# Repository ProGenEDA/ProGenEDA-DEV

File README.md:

# ProGenEDA

ProGenEDA is a development repository for deterministic, donor-aware EDA
generation. A backend receives one canonical circuit JSON document, resolves
only supported native records, produces an editable project, and retains
machine-readable validation evidence beside the result.

This repository contains independent backends for Proteus, KiCad, EasyEDA Pro,
and LTspice. They share the canonical circuit intent but do not depend on one
another at runtime.

## Backends

| Backend | Native output | Current entry point | Scope summary |
| --- | --- | --- | --- |
| Proteus | `.pdsprj` | [`proteus/active/`](proteus/active/) | Donor-backed placement, bounded terminal attachment, value editing, and local loader evidence. |
| KiCad | `.kicad_pro`, `.kicad_sch`, optional `.kicad_pcb` | [`kicad/`](kicad/) | Canonical JSON repair, source-backed schematic generation, combination routing, validation, and bounded two-layer PCB output. |
| EasyEDA Pro | `.eprj` | [`Easyeda/`](Easyeda/) | Native SQLite project generation using audited source records, compact schematic routing, and bounded PCB generation. |
| Altium | `.PrjPcb` + source-backed `.SchDoc`, packaged as ZIP | [`Altium/`](Altium/) | Full direct native schematic pipeline: repair, values, source selection, placement, arrangement, wiring/terminals, native emission, and saved-file validation. Direct PCB output is not qualified yet. |
| LTspice | `.asc` | [`ltspice/`](ltspice/) | Donor-native stock-symbol placement, physical-wire routing, and validated ASC emission. |

Each backend documents its supported catalogue, input restrictions, validation
contract, and release evidence in its own README. A backend must reject or
withhold unsupported work rather than substitute an approximate native record.

## Shared Generation Model

```text
Canonical circuit JSON
  -> normalize and validate input
  -> resolve supported components and pins
  -> place and arrange components
  -> route wires, terminals, or both according to backend policy
  -> edit approved values and references
  -> validate structure, pins, nets, geometry, and backend-specific rules
  -> emit native project plus internal audit artifacts
```

The canonical input remains the source of truth. Generation stages retain their
own reports and accepted or rejected layout/routing variants so a released
project can be traced back to the exact request and decisions that produced it.

## Getting Started

Run backend commands from the repository root. The portable executables are
the normal distribution form; direct source commands use the same pipeline.

### KiCad

```bash
unzip kicad/release/progen-kicad-portable-2026_07_17_kq26_clearance_v1.zip
./progen-kicad-portable/progen-kicad run INPUT.json \
  --output-root /tmp/progen-kicad-runs \
  --routing-mode combination
```

For PCB-only output from the same canonical input:

```bash
./progen-kicad-portable/progen-kicad run-pcb INPUT.json \
  --output-root /tmp/progen-kicad-pcb-runs \
  --routing-mode combination
```

Direct source entry point:

```bash
PYTHONPATH=. python -m kicad.pipeline.progen_kicad_executable run INPUT.json \
  --output-root /tmp/progen-kicad-runs \
  --routing-mode combination
```

See [`kicad/README.md`](kicad/README.md) for the supported input and
[`kicad/pcb/README.md`](kicad/pcb/README.md) for the physical-board boundary.

### EasyEDA Pro

```bash
Easyeda/dist/progen-easyeda run INPUT.json \
  --output-root /tmp/progen-easyeda-runs \
  --routing-mode combination \
  --events ndjson
```

Direct source entry point:

```bash
PYTHONPATH=. python -m Easyeda.executable run INPUT.json \
  --output-root /tmp/progen-easyeda-runs \
  --routing-mode combination \
  --events ndjson
```

See [`Easyeda/README.md`](Easyeda/README.md) and
[`Easyeda/SUPPORTED_COMPONENTS.md`](Easyeda/SUPPORTED_COMPONENTS.md).

### LTspice

```bash
PYTHONPATH=. python -m ltspice INPUT.json \
  --outdir /tmp/progen-ltspice-output \
  --label generated-circuit \
  --engine donor_native
```

The result is a native `.asc` file. The generator and deterministic validators
do not require LTspice to be installed; opening or simulating the output does.
See [`ltspice/README.md`](ltspice/README.md) for the donor-observed support
boundary and packaging instructions.

### Proteus

```powershell
.\proteus\active\release\ProgenProteus.exe generate `
  .\proteus\active\examples\progen_proteus_r_c_value_edit.json `
  --output .\out\r_c_terminalized.pdsprj
```

Direct source entry point:

```powershell
$env:PYTHONPATH = "proteus/active/src"
python -m proteusgen.proteus_cli generate `
  proteus/active/examples/progen_proteus_r_c_value_edit.json `
  --output out/r_c_terminalized.pdsprj
```

See [`proteus/active/README.md`](proteus/active/README.md) for the donor
policy, current terminal boundary, and native loader gate.

## Validation Principles

Every backend owns a deterministic validation path. Depending on the backend,
that includes component/reference checks, pin existence, expected-net
comparison, geometry and clearance checks, source-record provenance, native
file parsing, and optional application/CLI acceptance evidence.

Native application checks are additional evidence, not a substitute for the
backend's own structural validation. Conversely, static validation does not
promote a project that has not satisfied the backend's documented release
contract.

## Qualification Evidence

- KiCad: [`kicad/qualification/README.md`](kicad/qualification/README.md)
  documents the 400-circuit corpus and the bounded PCB results.
- EasyEDA Pro: [`Easyeda/qualification/README.md`](Easyeda/qualification/README.md)
  documents the 300-circuit full-pin corpus.
- LTspice: [`ltspice/docs/COMMON_CIRCUIT_CORPUS.md`](ltspice/docs/COMMON_CIRCUIT_CORPUS.md)
  describes the named native-circuit corpus.
- Proteus: [`proteus/active/examples/proteus_200_circuits/README.md`](proteus/active/examples/proteus_200_circuits/README.md)
  documents the executable-oriented corpus and evidence boundary.

## Repository Map

```text
proteus/    native Proteus backend, active package, donor evidence, experiments
kicad/      KiCad schematic and PCB generator, source pack, qualification, release
Easyeda/    independent EasyEDA Pro backend, audited donor bundle, qualification
Altium/     direct native Altium schematic generator, source pack, validators, research bridge
ltspice/    donor-native LTspice backend, catalogues, pipeline, packaging, tests
pspice/     PSpice/OrCAD research and early generator material
showcase/   curated generated projects for review
tests/      repository-level regression checks
```

Historical experiment folders are preserved as evidence. New generation runs
should create a new run directory and never overwrite prior outputs.

## Documentation Index

- [`kicad/FINALIZATION_STATUS.md`](kicad/FINALIZATION_STATUS.md) - KiCad
  status and release boundary.
- [`kicad/pipeline/MAIN_INPUT_JSON_CONTRACT.md`](kicad/pipeline/MAIN_INPUT_JSON_CONTRACT.md)
  - canonical KiCad input contract.
- [`Easyeda/INPUT_JSON.md`](Easyeda/INPUT_JSON.md) - EasyEDA input contract.
- [`Easyeda/ARCHITECTURE.md`](Easyeda/ARCHITECTURE.md) - EasyEDA stage design.
- [`Altium/README.md`](Altium/README.md) - Altium target status and commands.
- [`Altium/PIPELINE.md`](Altium/PIPELINE.md) - Altium stage contracts and immutable run artifacts.
- [`Altium/ARCHITECTURE.md`](Altium/ARCHITECTURE.md) - Altium stage contracts.
- [`Altium/INPUT_JSON.md`](Altium/INPUT_JSON.md) - Altium direct input contract.
- [`ltspice/ARCHITECTURE.md`](ltspice/ARCHITECTURE.md) - LTspice donor-native
  architecture and support evidence.
- [`proteus/active/docs/README.md`](proteus/active/docs/README.md) - Proteus
  operational documentation index.

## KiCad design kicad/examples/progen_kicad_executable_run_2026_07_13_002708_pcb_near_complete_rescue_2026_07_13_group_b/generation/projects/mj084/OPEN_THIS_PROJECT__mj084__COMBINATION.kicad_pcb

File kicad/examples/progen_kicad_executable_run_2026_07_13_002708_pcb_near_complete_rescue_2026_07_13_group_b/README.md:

# ProGenEDA KiCad Executable Run

This immutable folder was produced by the single executable wrapper. It first validates/fixes input JSON into canonical main JSON, then runs the KiCad combination/terminal/wire project pipeline. The generated project run contains user-project zips and internal-only bundles.

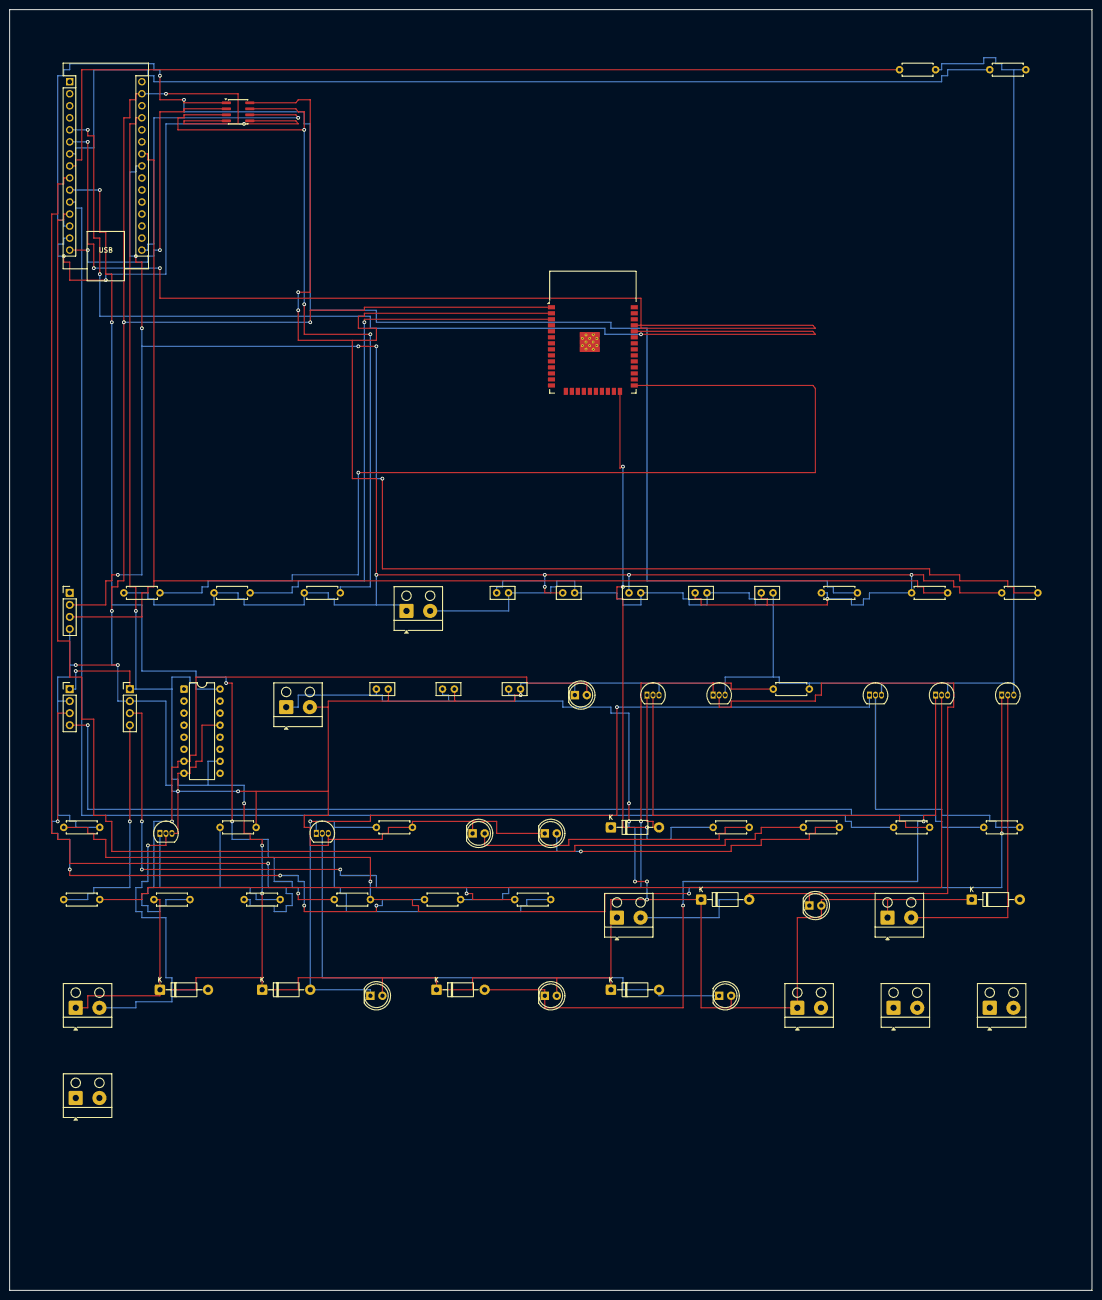
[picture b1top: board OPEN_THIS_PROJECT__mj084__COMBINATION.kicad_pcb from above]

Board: 2 copper layers, 228.6 x 270.5 mm, 67 parts (0 on the bottom side), 42 nets.

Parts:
B1_D1, B1_D2, B2_D1, B2_D2, B2_D3: Flyback diode; D_DO-41_SOD81_P10.16mm_Horizontal
B1_D3, B1_D4: Relay flyback diode; D_DO-41_SOD81_P10.16mm_Horizontal
B1_D5, B1_D6, B1_D7, B1_D8: Indicator LED; LED_D5.0mm
B1_J1, B1_J2, B1_J3, B1_J4: Screw terminal 2-pin; Altech_AK100_1x02_P5.00mm
B1_J5, B1_J6: PWM/control header; PinHeader_1x04_P2.54mm_Vertical
B1_Q1, B1_Q2, B2_Q1, B2_Q2: IRLZ44N; TO-92_Inline
B1_Q3, B1_Q4, B2_Q3: BC547; TO-92_Inline
B1_R1, B1_R2, B1_R3, B1_R4, B1_R5, B1_R6: Driver resistor; R_Axial_DIN0207_L6.3mm_D2.5mm_P7.62mm_Horizontal
B2_C1, B2_C2, B2_C3, B2_C4, B2_C5, B2_C6, B2_C7, B2_C8: 100nF; C_Disc_D5.0mm_W2.5mm_P2.50mm
B2_D4, B2_D5: Status LED; LED_D5.0mm
B2_J_3V3: 3V3 header; Altech_AK100_1x02_P5.00mm
B2_J_I2C: I2C header; PinHeader_1x04_P2.54mm_Vertical
B2_J_LOAD1: Load 1; Altech_AK100_1x02_P5.00mm
B2_J_LOAD2: Load 2; Altech_AK100_1x02_P5.00mm
B2_J_POWER: Power header; Altech_AK100_1x02_P5.00mm
B2_J_RELAY: Relay contact; Altech_AK100_1x02_P5.00mm
B2_R1, B2_R2, B2_R3, B2_R4, B2_R5, B2_R6, B2_R7, B2_R8, B2_R9, B2_R10, B2_R11, B2_R12, B2_R13, B2_R14, B2_R15: Resistor; R_Axial_DIN0207_L6.3mm_D2.5mm_P7.62mm_Horizontal
B2_U1: Arduino Nano; Arduino_Nano
B2_U2: ESP32-WROOM; ESP32-WROOM-32
B2_U6: W25Q64; SOIC-8_3.9x4.9mm_P1.27mm
B3_LED1: Logic LED; LED_D5.0mm
B3_R1: 220 ohm; R_Axial_DIN0207_L6.3mm_D2.5mm_P7.62mm_Horizontal
B3_U595: 74HC595; DIP-16_W7.62mm

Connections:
+3V3: B2_C4.1, B2_C5.1, B2_C6.1, B2_C7.1, B2_C8.1, B2_J_3V3.1, B2_R1.1, B2_R2.1, B2_R3.1, B2_R4.1, B2_R5.1, B2_R6.1, B2_U2.2, B2_U6.8
B1_LOAD2_LOW: B1_D2.2, B1_D6.1, B1_J2.2, B1_Q2.2
B1_MOSFET1_GATE: B1_Q1.1, B1_R1.2, B1_R2.1
B1_MOSFET2_GATE: B1_Q2.1, B1_R3.2, B1_R4.1
B1_MOTOR_LOW: B1_D1.2, B1_D5.1, B1_Q1.2
B1_PWM_LOAD_2: B1_J6.3, B1_R3.1
B1_PWM_MOTOR_1: B1_J5.3, B1_R1.1
B1_RELAY1_BASE: B1_Q3.2, B1_R5.2
B1_RELAY1_COIL_LOW: B1_D3.2, B1_D7.1, B1_Q3.1
B1_RELAY1_CTRL: B1_J5.4, B1_R5.1
B1_RELAY2_BASE: B1_Q4.2, B1_R6.2
B1_RELAY2_COIL_LOW: B1_D4.2, B1_D8.1, B1_Q4.1
B1_RELAY2_CTRL: B1_J6.4, B1_R6.1
B2_ARDUINO_TO_ESP_RX: B2_U1.5, B2_U2.34
B2_ARDUINO_TO_ESP_TX: B2_U1.6, B2_U2.35
B2_BUTTON_1: B2_R7.1, B2_U1.7
B2_BUTTON_2: B2_R8.1, B2_U1.8
B2_ESP_BOOT: B2_R6.2, B2_U2.25
B2_ESP_EN: B2_R5.2, B2_U2.3
B2_FLASH_WP_HOLD: B2_R4.2, B2_U6.3, B2_U6.7
B2_I2C_SCL: B2_J_I2C.3, B2_R2.2, B2_U1.24
B2_I2C_SDA: B2_J_I2C.2, B2_R1.2, B2_U1.23
B2_LED_STATUS_1: B2_R14.1, B2_U1.12
B2_LED_STATUS_1_A: B2_D4.2, B2_R14.2
B2_LED_STATUS_2: B2_R15.1, B2_U2.24
B2_LED_STATUS_2_A: B2_D5.2, B2_R15.2
B2_MOSFET1_GATE: B2_R9.1, B2_U1.9
B2_MOSFET1_GATE_NODE: B2_Q1.1, B2_R9.2, B2_R10.1
B2_MOSFET1_LOAD_LOW: B2_D1.2, B2_J_LOAD1.2, B2_Q1.2
B2_MOSFET2_GATE: B2_R11.1, B2_U1.10
B2_MOSFET2_GATE_NODE: B2_Q2.1, B2_R11.2, B2_R12.1
B2_MOSFET2_LOAD_LOW: B2_D2.2, B2_J_LOAD2.2, B2_Q2.2
B2_RELAY_BASE: B2_Q3.2, B2_R13.2
B2_RELAY_COIL_LOW: B2_D3.2, B2_Q3.1
B2_RELAY_CTRL: B2_R13.1, B2_U1.11
B2_SPI_CS_FLASH: B2_R3.2, B2_U1.13, B2_U6.1
B2_SPI_MISO: B2_U1.15, B2_U6.2
B2_SPI_MOSI: B2_U1.14, B2_U6.5
B2_SPI_SCK: B2_U1.16, B2_U6.6
B3_LED_LOGIC_A: B3_LED1.2, B3_R1.2, B3_U595.7
GUESS_TERMINAL_5V: B1_D1.1, B1_D2.1, B1_D3.1, B1_D4.1, B1_D5.2, B1_D6.2, B1_D7.2, B1_D8.2, B1_J1.1, B1_J2.1, B1_J5.1, B1_J6.1, B2_C1.1, B2_C2.1, B2_C3.1, B2_D1.1, B2_D2.1, B2_D3.1, B2_J_LOAD1.1, B2_J_LOAD2.1, B2_J_POWER.1, B2_U1.27, B3_R1.1, B3_U595.10, B3_U595.16
GUESS_TERMINAL_GND: B1_J5.2, B1_J6.2, B1_Q1.3, B1_Q2.3, B1_Q3.3, B1_Q4.3, B1_R2.2, B1_R4.2, B2_C1.2, B2_C2.2, B2_C3.2, B2_C4.2, B2_C5.2, B2_C6.2, B2_C7.2, B2_C8.2, B2_D4.1, B2_D5.1, B2_J_3V3.2, B2_J_I2C.4, B2_J_POWER.2, B2_Q1.3, B2_Q2.3, B2_Q3.3, B2_R7.2, B2_R8.2, B2_R10.2, B2_R12.2, B2_U1.29, B2_U2.1, B2_U6.4, B3_LED1.1, B3_U595.8, B3_U595.13

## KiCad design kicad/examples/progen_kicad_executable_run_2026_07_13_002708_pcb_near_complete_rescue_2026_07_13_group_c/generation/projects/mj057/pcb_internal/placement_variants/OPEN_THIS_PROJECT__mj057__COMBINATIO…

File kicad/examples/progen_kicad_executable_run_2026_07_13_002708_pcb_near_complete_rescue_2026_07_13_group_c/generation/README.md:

# Final JSON To KiCad Combination Project Run

This folder is an immutable generated record. It takes connected final JSON files, runs the arrangement decider, beautifier, routing/terminal planner, and KiCad backend emitter, then writes openable KiCad projects with real embedded symbols plus wire objects. Terminal/local-label objects are only valid when the run is generated in terminal or combination mode.

The wire planner is fed exact KiCad source-symbol pin points through `routing_inputs/` when those pins can be resolved. The wire maker uses the same source-backed KiCad pin geometry when possible. Any unresolved pin aliases, unroutable nets, strict-wire connectivity violations, local expected-net comparison failures, wire crossings, and wire/component body contacts are recorded in each project manifest.

Each project also has a two-artifact output boundary under `outputs/<circuit_id>/`: `user_project/PROGEN_KICAD_PROJECT.zip` is the only user-downloadable export, while `internal/internal_bundle.zip` is backend-only metadata containing the main input JSON, all generated stage JSON, validation reports, and retained arrangement variants with the accepted variant marked.

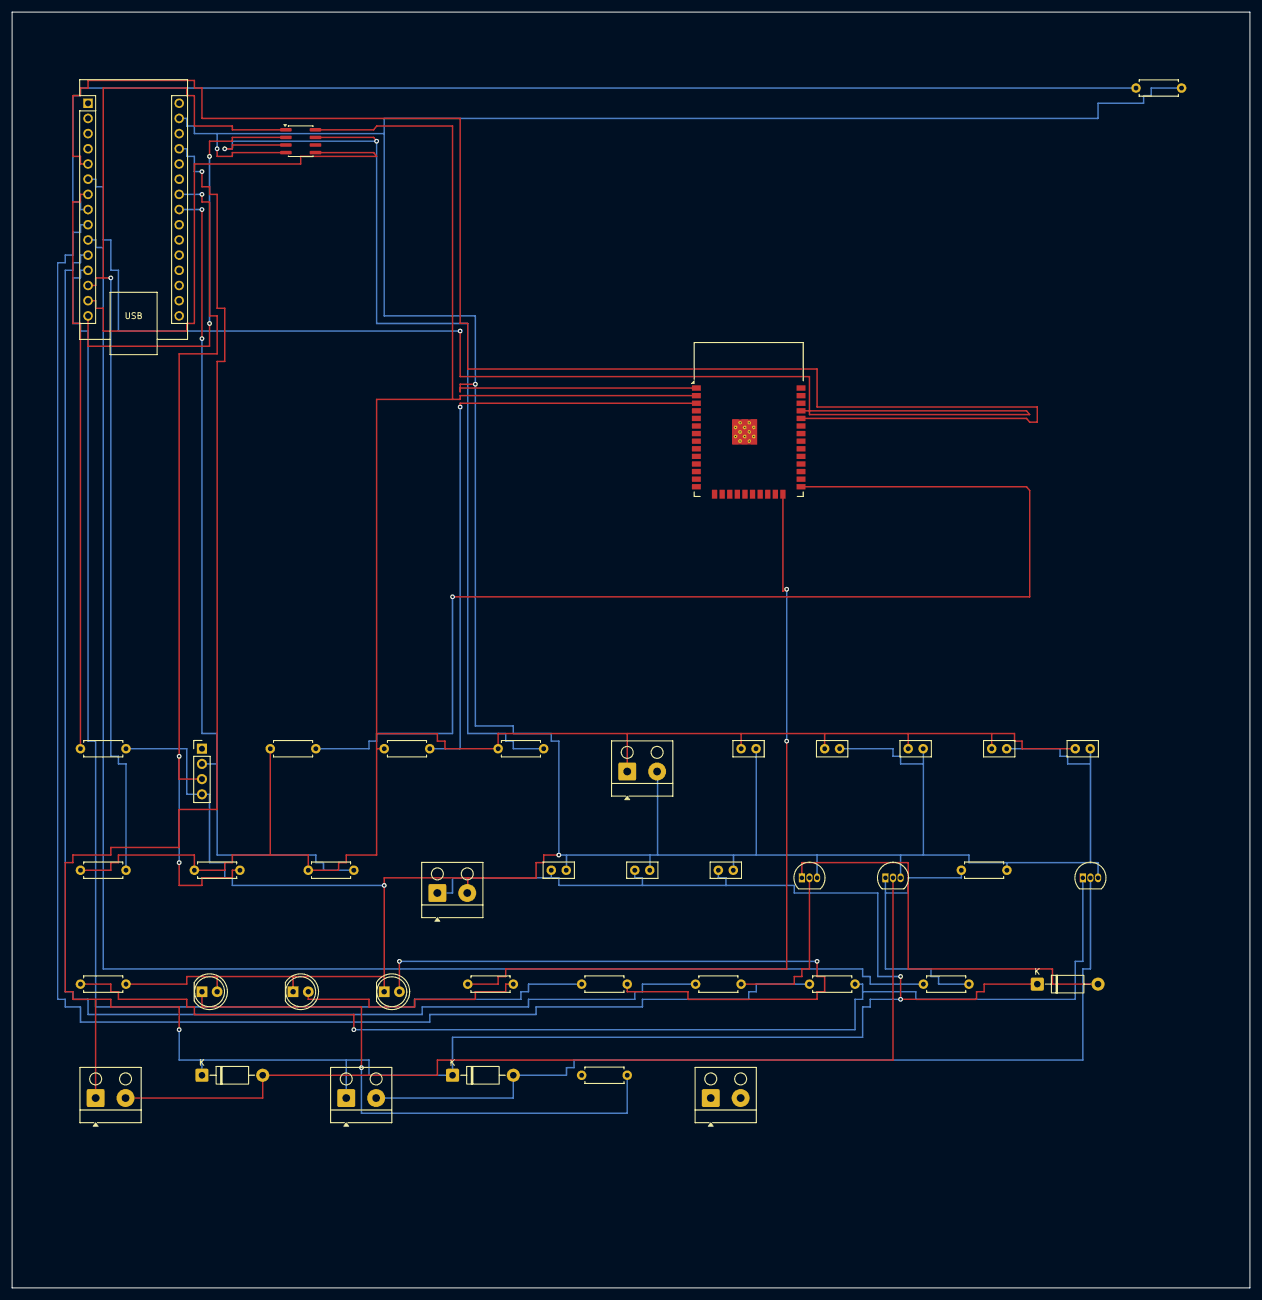
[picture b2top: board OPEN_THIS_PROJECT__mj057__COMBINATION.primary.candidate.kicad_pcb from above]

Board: 2 copper layers, 207.0 x 213.4 mm, 42 parts (0 on the bottom side), 30 nets.

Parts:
B1_C1, B1_C2, B1_C3, B1_C4, B1_C5, B1_C6, B1_C7, B1_C8: 100nF; C_Disc_D5.0mm_W2.5mm_P2.50mm
B1_D1, B1_D2, B1_D3: Flyback diode; D_DO-41_SOD81_P10.16mm_Horizontal
B1_D4, B1_D5: Status LED; LED_D5.0mm
B1_J_3V3: 3V3 header; Altech_AK100_1x02_P5.00mm
B1_J_I2C: I2C header; PinHeader_1x04_P2.54mm_Vertical
B1_J_LOAD1: Load 1; Altech_AK100_1x02_P5.00mm
B1_J_LOAD2: Load 2; Altech_AK100_1x02_P5.00mm
B1_J_POWER: Power header; Altech_AK100_1x02_P5.00mm
B1_J_RELAY: Relay contact; Altech_AK100_1x02_P5.00mm
B1_Q1, B1_Q2: IRLZ44N; TO-92_Inline
B1_Q3: BC547; TO-92_Inline
B1_R1, B1_R2, B1_R3, B1_R4, B1_R5, B1_R6, B1_R7, B1_R8, B1_R9, B1_R10, B1_R11, B1_R12, B1_R13, B1_R14, B1_R15: Resistor; R_Axial_DIN0207_L6.3mm_D2.5mm_P7.62mm_Horizontal
B1_U1: Arduino Nano; Arduino_Nano
B1_U2: ESP32-WROOM; ESP32-WROOM-32
B1_U6: W25Q64; SOIC-8_3.9x4.9mm_P1.27mm
B2_LED1: Logic LED; LED_D5.0mm
B2_R1: 220 ohm; R_Axial_DIN0207_L6.3mm_D2.5mm_P7.62mm_Horizontal

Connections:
+3V3: B1_C4.1, B1_C5.1, B1_C6.1, B1_C7.1, B1_C8.1, B1_J_3V3.1, B1_R1.1, B1_R2.1, B1_R3.1, B1_R4.1, B1_R5.1, B1_R6.1, B1_U2.2, B1_U6.8
+5V: B1_C1.1, B1_C2.1, B1_C3.1, B1_D1.1, B1_D2.1, B1_D3.1, B1_J_LOAD1.1, B1_J_LOAD2.1, B1_J_POWER.1, B1_U1.27
B1_ARDUINO_TO_ESP_RX: B1_U1.5, B1_U2.34
B1_ARDUINO_TO_ESP_TX: B1_U1.6, B1_U2.35
B1_BUTTON_1: B1_R7.1, B1_U1.7
B1_BUTTON_2: B1_R8.1, B1_U1.8
B1_ESP_BOOT: B1_R6.2, B1_U2.25
B1_ESP_EN: B1_R5.2, B1_U2.3
B1_FLASH_WP_HOLD: B1_R4.2, B1_U6.3, B1_U6.7
B1_I2C_SCL: B1_J_I2C.3, B1_R2.2, B1_U1.24
B1_I2C_SDA: B1_J_I2C.2, B1_R1.2, B1_U1.23
B1_LED_STATUS_1: B1_R14.1, B1_U1.12
B1_LED_STATUS_1_A: B1_D4.2, B1_R14.2
B1_LED_STATUS_2: B1_R15.1, B1_U2.24
B1_LED_STATUS_2_A: B1_D5.2, B1_R15.2
B1_MOSFET1_GATE: B1_R9.1, B1_U1.9
B1_MOSFET1_GATE_NODE: B1_Q1.1, B1_R9.2, B1_R10.1
B1_MOSFET1_LOAD_LOW: B1_D1.2, B1_J_LOAD1.2, B1_Q1.2
B1_MOSFET2_GATE: B1_R11.1, B1_U1.10
B1_MOSFET2_GATE_NODE: B1_Q2.1, B1_R11.2, B1_R12.1
B1_MOSFET2_LOAD_LOW: B1_D2.2, B1_J_LOAD2.2, B1_Q2.2
B1_RELAY_BASE: B1_Q3.2, B1_R13.2
B1_RELAY_COIL_LOW: B1_D3.2, B1_Q3.1
B1_RELAY_CTRL: B1_R13.1, B1_U1.11
B1_SPI_CS_FLASH: B1_R3.2, B1_U1.13, B1_U6.1
B1_SPI_MISO: B1_U1.15, B1_U6.2
B1_SPI_MOSI: B1_U1.14, B1_U6.5
B1_SPI_SCK: B1_U1.16, B1_U6.6
B2_LED_A: B2_LED1.1, B2_R1.2
GND: B1_C1.2, B1_C2.2, B1_C3.2, B1_C4.2, B1_C5.2, B1_C6.2, B1_C7.2, B1_C8.2, B1_D4.1, B1_D5.1, B1_J_3V3.2, B1_J_I2C.4, B1_J_POWER.2, B1_Q1.3, B1_Q2.3, B1_Q3.3, B1_R7.2, B1_R8.2, B1_R10.2, B1_R12.2, B1_U1.29, B1_U2.1, B1_U6.4, B2_LED1.2

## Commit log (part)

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2026-06-10 Add exact IC rezip diagnostics
2026-06-10 Add IC pairwise donor matrix
2026-06-10 Regenerate IC pairwise matrix with CDB fixes
2026-06-10 Add focused IC pairwise error sample
2026-06-10 Expand focused IC pairwise error repairs
2026-06-10 Expand pairwise combinational method probes
2026-06-10 Add sequential pair master metadata probe
2026-06-11 Import manual Proteus donor projects
2026-06-11 Add KiCad generator workspace and source scan targets
2026-06-11 Add KiCad source scan notes
2026-06-11 Add OrCAD/PSpice visual generator plan
2026-06-11 Add durable OrCAD visual generator scaffold
2026-06-11 Add OrCAD/PSpice CircuitIR example
2026-06-11 Add generator README
2026-06-11 Add PSpice status report
2026-06-11 Add KiCad generator workspace README
2026-06-11 Add KiCad visual generator starter script
2026-06-11 Add KiCad generator start analysis report
2026-06-11 Add KiCad EE-215 diode IV example CircuitIR
2026-06-11 Add KiCad RC low-pass example CircuitIR
2026-06-11 Update KiCad README with generator start status
2026-06-11 Fix KiCad wire generation and clearer output names
2026-06-11 Add KiCad project symbol fixer and downloader
2026-06-11 Add KiCad tools README
2026-06-11 Record KiCad V2 missing symbols and autolib fix
2026-06-11 Record KiCad V3 missing symbols and V4 embedded-symbol fix
2026-06-11 Record KiCad V4 parse failure and manual donor request
2026-06-11 Add KiCad GitHub auto downloader tool
2026-06-11 Document KiCad GitHub auto downloader
2026-06-11 Update KiCad tools README with GitHub downloader
2026-06-11 Add double-click KiCad GitHub downloader BAT
2026-06-11 Add double-click KiCad human circuit downloader
2026-06-11 Add KiCad source parser writer deep dive report
2026-06-11 Add KiCad GPL reuse decision note
2026-06-11 Add KiCad source file pack manifest report
2026-06-11 Add KiCad source pack analysis report
2026-06-11 Add KiCad V5 source-driven generator report
2026-06-11 Document KiCad V5 source-driven artifact
2026-06-11 Add KiCad V6 pin endpoint autoroute report
2026-06-11 Add KiCad V7 component catalog
2026-06-11 Add KiCad component master plan
2026-06-11 Promote KiCad backend package
2026-06-11 Add KiCad S-expression helpers
2026-06-11 Add KiCad project writer
2026-06-11 Add KiCad schematic static validator
2026-06-11 Update KiCad generator README for V7 component catalog
2026-06-11 Add KiCad V8 true 50 component zoo generator
2026-06-11 Add KiCad V8 50 component zoo report
2026-06-12 Add KiCad CircuitIR generation rulebook
2026-06-12 Add KiCad local JSON project generator
2026-06-12 Repair accidental KiCad generator placeholder
2026-06-12 Record ProgenLive IC prompt errors and fixes
2026-06-12 Record ProgenLive IC prompt failures and fixes
2026-06-12 Add reset-safe NAND flip-flop fix
2026-06-15 Add component placer analysis runner
2026-06-15 Add autonomous Camber analyzer script
2026-06-21 Recover component placer pipeline state
2026-06-21 Add guarded beautifier coordinate baseline
2026-06-21 Expand beautifier distance and large rule tests
2026-06-21 Add V4 visible packet beautifier stage
2026-06-23 Add promoted mega donors and architecture notes
2026-06-23 Record active beautifier workflow
2026-06-23 Add passive family beautifier probe
2026-06-24 Add parsed resistor beautifier probe
2026-06-24 Add R91 resistor beautifier stress probe
2026-06-24 Add reusable CAP beautifier probe
2026-06-24 Add CAP 100 beautifier stress probe
2026-06-24 Add base135 beautifier probes for component families
2026-06-24 Add mixed base135 beautifier stress pack
2026-06-25 Add isolated non-IC beautifier probes
2026-06-25 Fix display layout and exact control counts
2026-06-25 Beautify exact controls and correct D20 placement
2026-06-25 Add family-researched IC beautifier acceptance pack
2026-06-26 Add footprint-aware IC beautifier packing
2026-06-26 Add value changer and terminal placer probes
2026-06-28 Fix value mutation and expand terminal probes
2026-06-28 Consolidate Progen repository and documentation
2026-06-29 Add resistor-specific attached terminal stage
2026-06-29 Add shared capacitor terminal attachment stage
2026-06-29 Add donor-proven REALIND terminal attachment
2026-06-30 Rebuild capacitor terminal attachment from trusted donor
2026-06-30 Add donor-derived REALIND terminal attachment
2026-06-30 Add multi-family two-pin terminal checkpoint
2026-06-30 Add selective mixed terminal checkpoint
